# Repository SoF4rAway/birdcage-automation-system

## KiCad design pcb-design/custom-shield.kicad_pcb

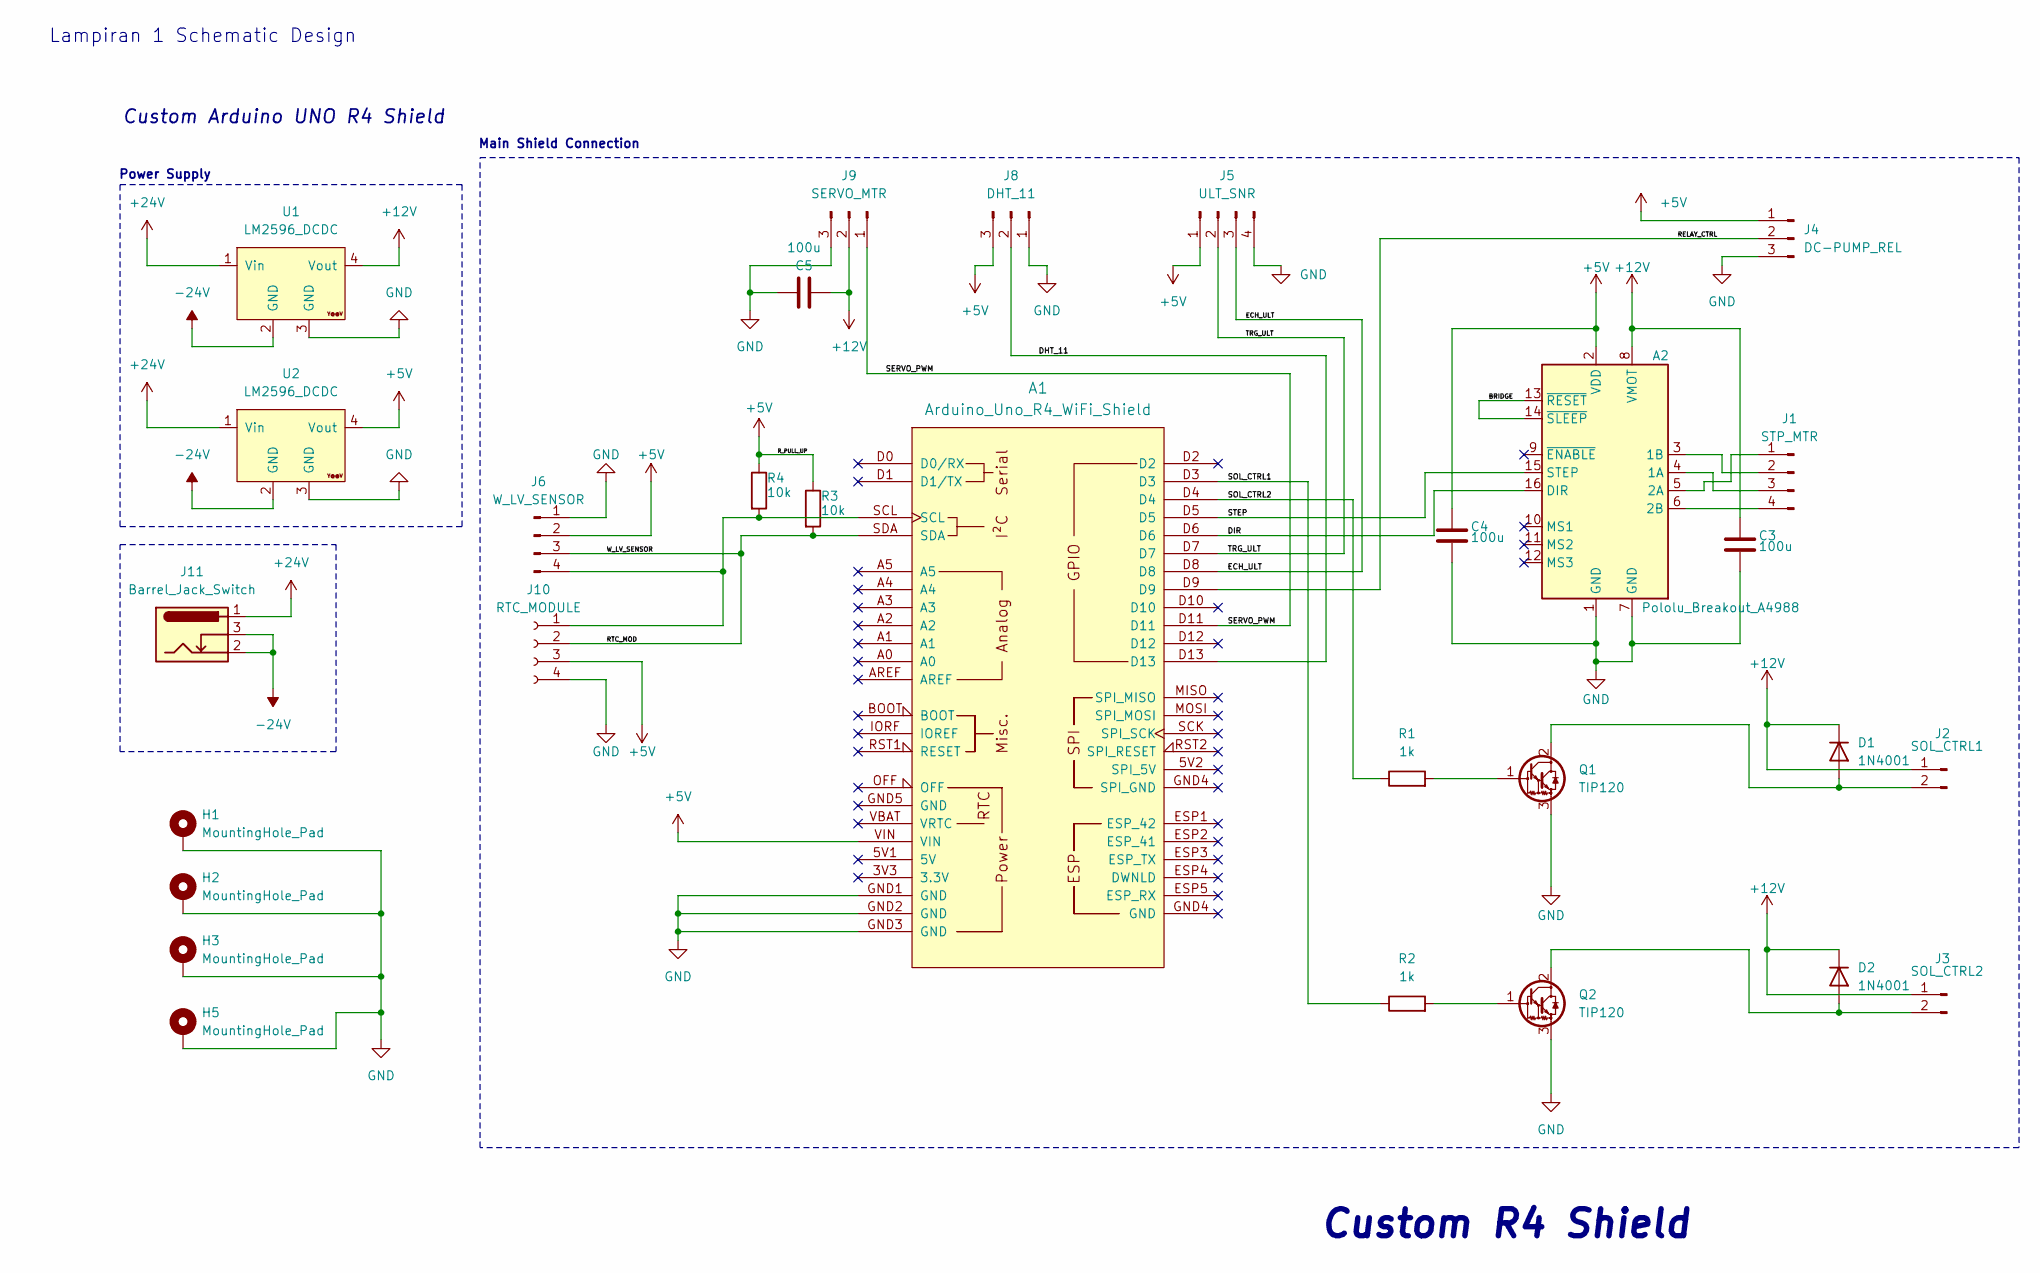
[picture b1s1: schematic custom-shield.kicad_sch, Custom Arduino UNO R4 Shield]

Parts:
A1: Arduino_Uno_R4_WiFi_Shield
A2: Pololu_Breakout_A4988; Pololu_Breakout-16_15.2x20.3mm
C3, C4, C5: 100u; CP_EIA-6032-28_Kemet-C_Pad2.25x2.35mm_HandSolder
D1, D2: 1N4001; D_DO-41_SOD81_P10.16mm_Horizontal
H1, H2, H3, H5: MountingHole_Pad; MountingHole_2.2mm_M2_DIN965_Pad
J1: STP_MTR; JST_PH_S4B-PH-K_1x04_P2.00mm_Horizontal
J2: SOL_CTRL1; JST_PH_S2B-PH-K_1x02_P2.00mm_Horizontal
J3: SOL_CTRL2; JST_PH_S2B-PH-K_1x02_P2.00mm_Horizontal
J4: DC-PUMP_REL; JST_PH_S3B-PH-K_1x03_P2.00mm_Horizontal
J5: ULT_SNR; JST_PH_S4B-PH-K_1x04_P2.00mm_Horizontal
J6: W_LV_SENSOR; JST_PH_S4B-PH-K_1x04_P2.00mm_Horizontal
J8: DHT_11; JST_PH_S3B-PH-K_1x03_P2.00mm_Horizontal
J9: SERVO_MTR; JST_PH_S3B-PH-K_1x03_P2.00mm_Horizontal
J10: RTC_MODULE; PinSocket_1x04_P2.54mm_Horizontal
J11: Barrel_Jack_Switch; CUI_PJ-002A
Q1, Q2: TIP120; TO-220-3_Vertical
R1, R2: 1k; R_0805_2012Metric_Pad1.20x1.40mm_HandSolder
R3, R4: 10k; R_0805_2012Metric_Pad1.20x1.40mm_HandSolder
U1, U2: LM2596_DCDC; YAAJ_DCDC_StepDown_LM2596

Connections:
+5V: A1.VIN, A2.2 (VDD), C4.1, J4.1, J5.1, J6.2, J8.3, J10.3, R3.1, R4.1, U2.4 (Vout)
+12V: A2.8 (VMOT), C3.1, C5.1, D1.1 (K), D2.1 (K), J2.1, J3.1, J9.2, U1.4 (Vout)
+24V: J11.1, U1.1 (Vin), U2.1 (Vin)
-24V: J11.2, J11.3, U1.2 (GND), U2.2 (GND)
/BRIDGE: A2.13 (~RESET), A2.14 (~SLEEP)
/DHT_11: A1.D13, J8.2
/DIR: A1.D6, A2.16 (DIR)
/ECH_ULT: A1.D8, J5.3
/RELAY_CTRL: A1.D9, J4.2
/RTC_MOD: A1.SDA, J6.3, J10.2, R3.2
/SERVO_PWM: A1.D11, J9.1
/SOL_CTRL1: A1.D3, R2.1
/SOL_CTRL2: A1.D4, R1.1
/STEP: A1.D5, A2.15 (STEP)
/TRG_ULT: A1.D7, J5.2
GND: A1.GND1 (GND), A1.GND2 (GND), A1.GND3 (GND), A2.1 (GND), A2.7 (GND), C3.2, C4.2, C5.2, H1.1, H2.1, H3.1, H5.1, J4.3, J5.4, J6.1, J8.1, J9.3, J10.4, Q1.3 (E), Q2.3 (E), U1.3 (GND), U2.3 (GND)
unnamed: A2.4 (1A), J1.3
unnamed: A2.3 (1B), J1.2
unnamed: A2.5 (2A), J1.1
unnamed: A2.6 (2B), J1.4
unnamed: D1.2 (A), J2.2, Q1.2 (C)
unnamed: D2.2 (A), J3.2, Q2.2 (C)
unnamed: A1.SCL, J6.4, J10.1, R4.2
unnamed: Q1.1 (B), R1.2
unnamed: Q2.1 (B), R2.2

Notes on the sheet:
Custom Arduino UNO R4 Shield
Power Supply
Main Shield Connection
Custom R4 Shield
Lampiran 1 Schematic Design

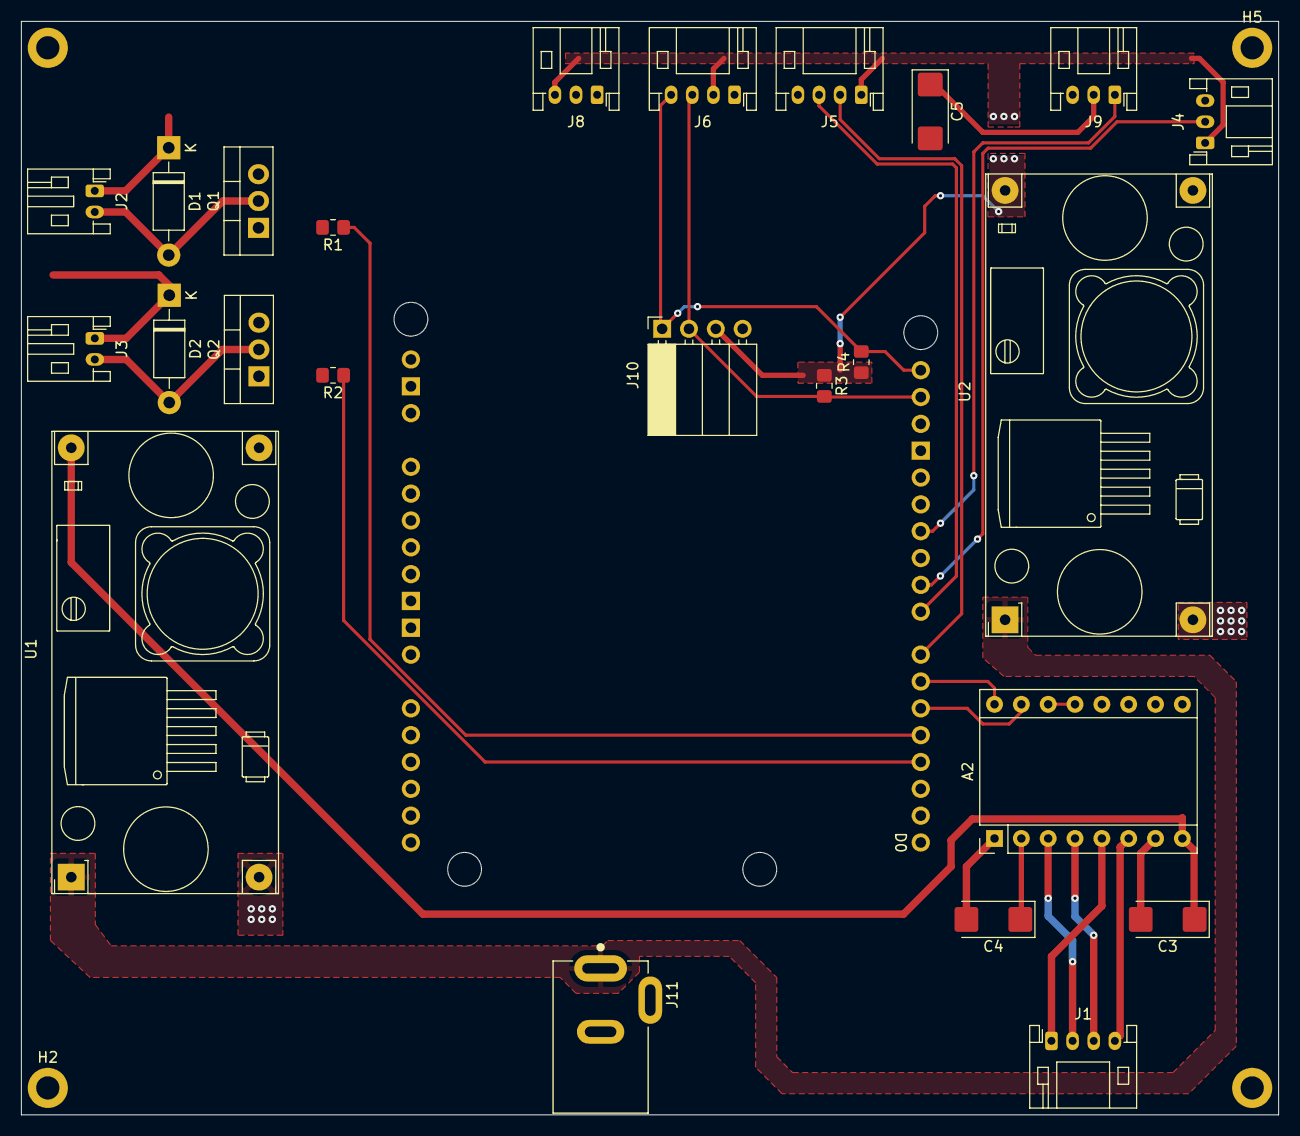
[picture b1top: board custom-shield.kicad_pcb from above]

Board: 2 copper layers, 119.0 x 103.5 mm, 29 parts (0 on the bottom side), 25 nets.

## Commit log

2025-05-24 Create LICENSE
